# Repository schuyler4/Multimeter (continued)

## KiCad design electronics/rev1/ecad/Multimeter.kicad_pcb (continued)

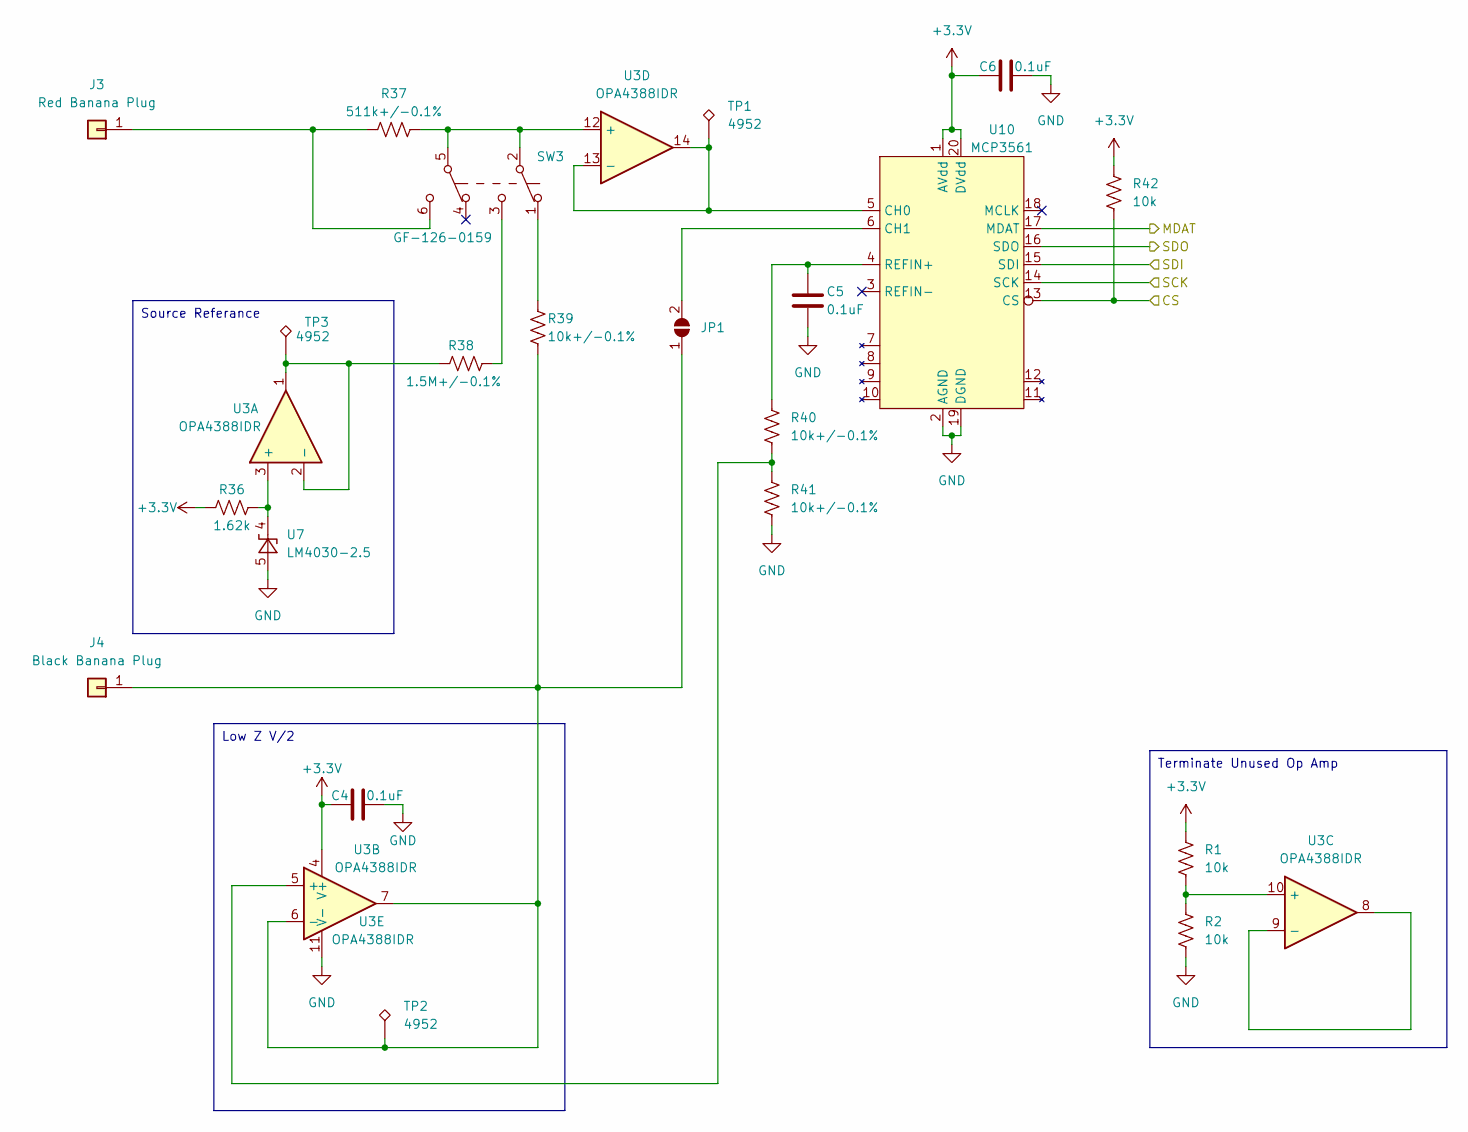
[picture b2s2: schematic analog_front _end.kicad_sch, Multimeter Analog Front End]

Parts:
C4, C5, C6: 0.1uF; C_0805_2012Metric; Part # CL21B104KBCNNNC; Digikey Part # 1276-1003-1-ND
J3: Red Banana Plug; KEYSTONE_575-4; Part # 575-8; Digikey Part # 36-575-8-ND
J4: Black Banana Plug; KEYSTONE_575-4; Part # 575-8; Digikey Part # 36-575-8-ND
JP1: SolderJumper-2_P1.3mm_Open_Pad1.0x1.5mm
R1, R2, R42: 10k; R_0805_2012Metric_Pad1.20x1.40mm_HandSolder; Part # RMCF0805FT10K0; Digikey Part # RMCF0805FT10K0CT-ND
R36: 1.62k; R_0805_2012Metric_Pad1.20x1.40mm_HandSolder; Part # RMCF0805FT1K62; Digikey Part # RMCF0805FT1K62CT-ND
R37: 511k+/-0.1%; R_0805_2012Metric_Pad1.20x1.40mm_HandSolder; Part # ERA-6AEB5113V; Digikey Part # P511KDACT-ND
R38: 1.5M+/-0.1%; R_0805_2012Metric_Pad1.20x1.40mm_HandSolder; Part # RG2012P-155-B-T5; Digikey Part # 408-2025-1-ND
R39, R40, R41: 10k+/-0.1%; R_0805_2012Metric_Pad1.20x1.40mm_HandSolder; Part # ERA-6AEB103V; Digikey Part # P10KDACT-ND
SW3: GF-126-0159; SW_GF-126-0159; Part # GF-126-0159; Digikey Part # SW342-ND
TP1, TP2, TP3: 4952; TestPoint_THTPad_1.5x1.5mm_Drill0.7mm; Part # 4952; Digikey Part # 36-4952-ND
U3: OPA4388IDR; SOIC-14_3.9x8.7mm_P1.27mm; Part # OPA4388IDR; Digikey Part # 296-53511-1-ND
U7: LM4030-2.5; SOT-23-5; Part # LM4030CMF-2.5/NOPB; Digikey Part # LM4030CMF-2.5/NOPBCT-ND
U10: MCP3561; SSOP-20_4.4x6.5mm_P0.65mm; Part # MCP3561RT-E/ST; Digikey Part # 150-MCP3561RT-E/STCT-ND

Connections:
+3.3V: C4.1, C6.1, R1.1, R36.1, R42.1, U3.4 (V+), U10.1 (AVdd), U10.20 (DVdd); also elsewhere on the board
/Analog Front End/CS: R42.2, U10.13 (CS); also elsewhere on the board
/Analog Front End/MDAT: U10.17 (MDAT); also elsewhere on the board
/Analog Front End/SCK: U10.14 (SCK); also elsewhere on the board
/Analog Front End/SDI: U10.15 (SDI); also elsewhere on the board
/Analog Front End/SDO: U10.16 (SDO); also elsewhere on the board
GND: C4.2, C5.2, C6.2, R2.2, R41.2, U3.11 (V-), U7.5 (A), U10.2 (AGND), U10.19 (DGND); also elsewhere on the board
unnamed: J3.1, R37.1, SW3.6 (C)
unnamed: J4.1, JP1.1 (A), R39.2, TP2.1, U3.6 (-), U3.7
unnamed: JP1.2 (B), U10.6 (CH1)
unnamed: R38.2, SW3.3 (C)
unnamed: R39.1, SW3.1 (A)
unnamed: R36.2, U3.3 (+), U7.4 (K)
unnamed: R38.1, TP3.1, U3.1, U3.2 (-)
unnamed: R40.2, R41.1, U3.5 (+)
unnamed: R1.2, R2.1, U3.10 (+)
unnamed: U3.8, U3.9 (-)
unnamed: R37.2, SW3.2 (B), SW3.5 (B), U3.12 (+)
unnamed: TP1.1, U3.13 (-), U3.14, U10.5 (CH0)
unnamed: C5.1, R40.1, U10.4 (REFIN+)

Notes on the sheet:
Low Z V/2
Terminate Unused Op Amp
Source Referance

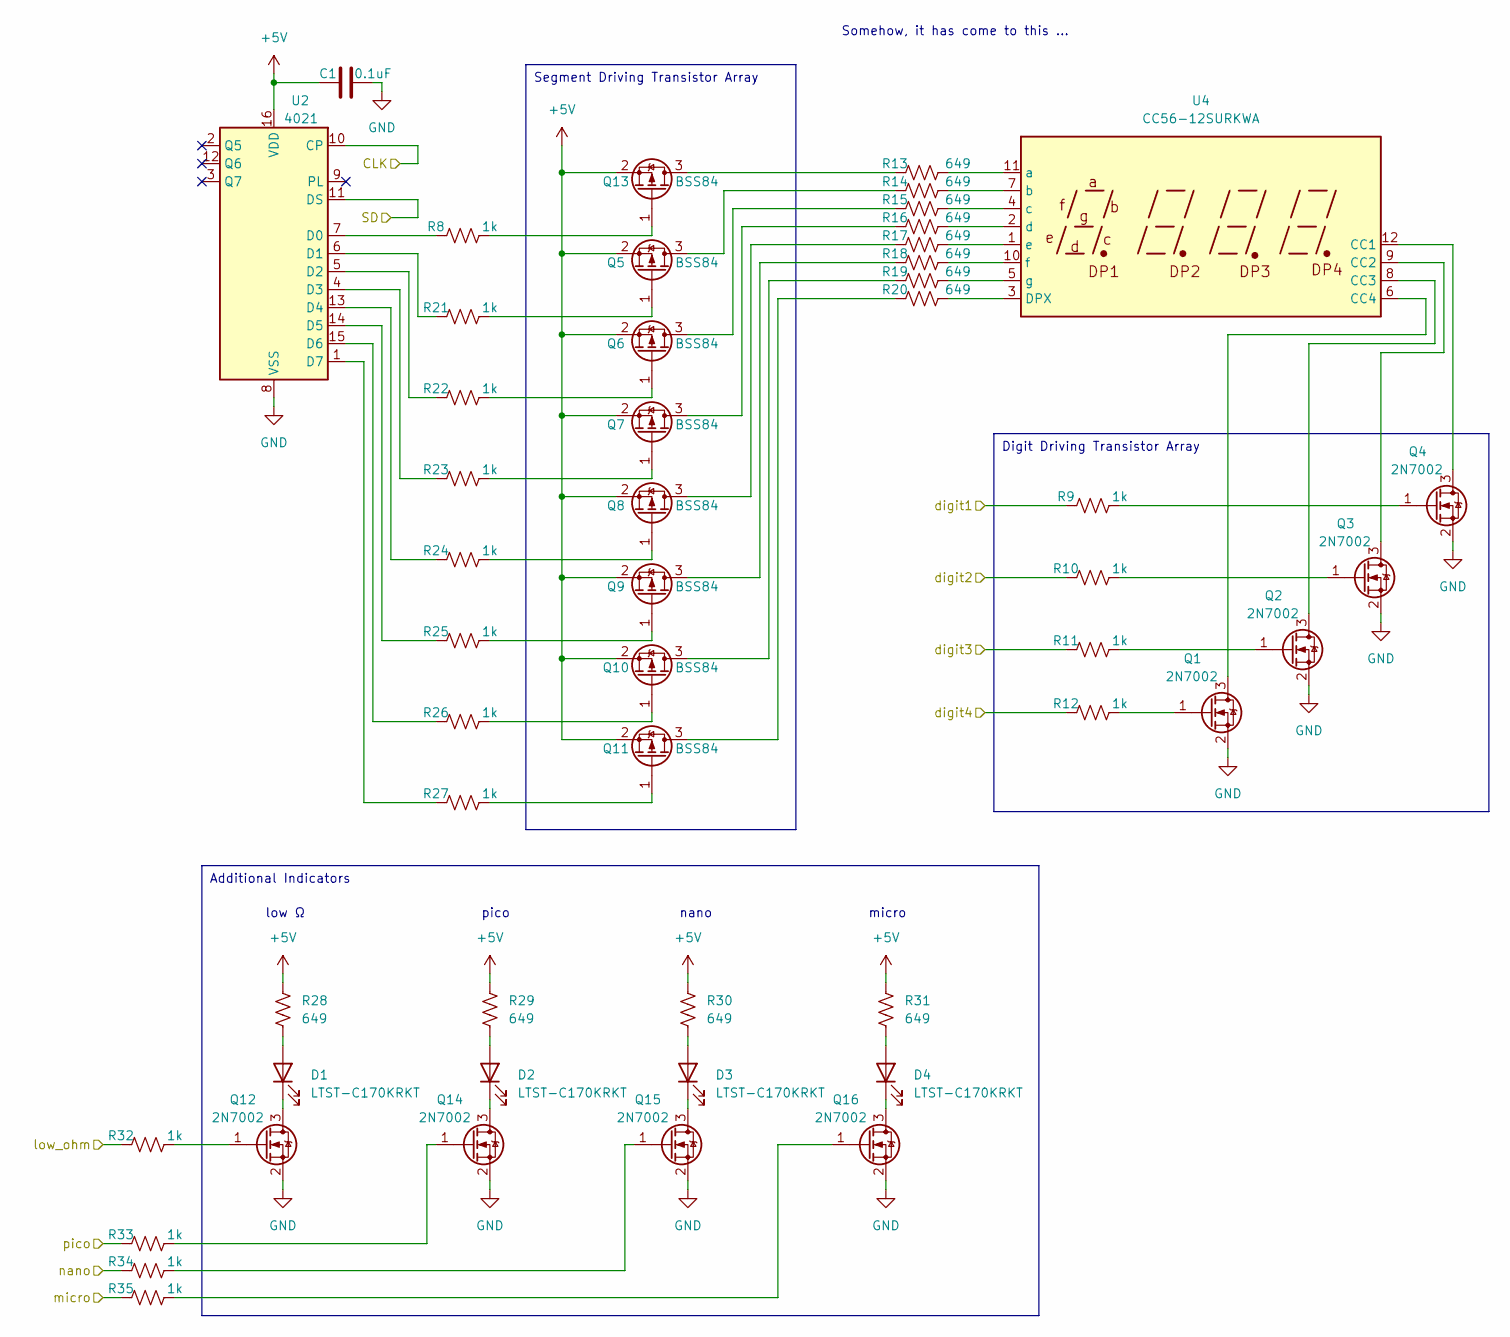
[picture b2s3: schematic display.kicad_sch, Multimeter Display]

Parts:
C1: 0.1uF; C_0805_2012Metric; Part # CL21B104KBCNNNC; Digikey Part # 1276-1003-1-ND
D1, D2, D3, D4: LTST-C170KRKT; LED_0805_2012Metric; Part # LTST-C170KRKT; Digikey Part # 160-1415-1-ND
Q1, Q2, Q3, Q4, Q12, Q14, Q15, Q16: 2N7002; SOT-23; Part # 2N7002; Digikey Part # 2N7002NCT-ND
Q5, Q6, Q7, Q8, Q9, Q10, Q11, Q13: BSS84; SOT-23; Part # BSS84; Digikey Part # 4786-BSS84CT-ND
R8, R9, R10, R11, R12, R21, R22, R23, R24, R25, R26, R27, R32, R33, R34, R35: 1k; R_0805_2012Metric_Pad1.20x1.40mm_HandSolder; Part # RMCF0805FT1K00; Digikey Part # RMCF0805FT1K00CT-ND
R13, R14, R15, R16, R17, R18, R19, R20, R28, R29, R30, R31: 649; R_0805_2012Metric_Pad1.20x1.40mm_HandSolder; Part # RMCF0805FT649R; Digikey Part # RMCF0805FT649RCT-ND
U2: 4021; SOIC-16_3.9x9.9mm_P1.27mm; Part # CD4021BM96; Digikey Part # 296-38905-1-ND
U4: CC56-12SURKWA; CA56-12SURKWA; Part # CC56-12SURKWA; Digikey Part # 754-CC56-12SURKWA-ND

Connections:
+5V: C1.1, Q5.2 (S), Q6.2 (S), Q7.2 (S), Q8.2 (S), Q9.2 (S), Q10.2 (S), Q11.2 (S), Q13.2 (S), R28.1, R29.1, R30.1, R31.1, U2.16 (VDD); also elsewhere on the board
/Display/CLK: U2.10 (CP); also elsewhere on the board
/Display/SD: U2.11 (DS); also elsewhere on the board
/Display/digit1: R9.1; also elsewhere on the board
/Display/digit2: R10.1; also elsewhere on the board
/Display/digit3: R11.1; also elsewhere on the board
/Display/digit4: R12.1; also elsewhere on the board
/Display/low_ohm: R32.1; also elsewhere on the board
/Display/micro: R35.1; also elsewhere on the board
/Display/nano: R34.1; also elsewhere on the board
/Display/pico: R33.1; also elsewhere on the board
GND: C1.2, Q1.2 (S), Q2.2 (S), Q3.2 (S), Q4.2 (S), Q12.2 (S), Q14.2 (S), Q15.2 (S), Q16.2 (S), U2.8 (VSS); also elsewhere on the board
unnamed: D1.2 (A), R28.2
unnamed: D1.1 (K), Q12.3 (D)
unnamed: D2.2 (A), R29.2
unnamed: D2.1 (K), Q14.3 (D)
unnamed: D3.2 (A), R30.2
unnamed: D3.1 (K), Q15.3 (D)
unnamed: D4.2 (A), R31.2
unnamed: D4.1 (K), Q16.3 (D)
unnamed: Q1.3 (D), U4.6 (CC4)
unnamed: Q1.1 (G), R12.2
unnamed: Q2.3 (D), U4.8 (CC3)
unnamed: Q2.1 (G), R11.2
unnamed: Q3.3 (D), U4.9 (CC2)
unnamed: Q3.1 (G), R10.2
unnamed: Q4.3 (D), U4.12 (CC1)
unnamed: Q4.1 (G), R9.2
unnamed: Q5.3 (D), R14.1
unnamed: Q5.1 (G), R21.2
unnamed: Q6.3 (D), R15.1
unnamed: Q6.1 (G), R22.2
unnamed: Q7.3 (D), R16.1
unnamed: Q7.1 (G), R23.2
unnamed: Q8.3 (D), R17.1
unnamed: Q8.1 (G), R24.2
unnamed: Q9.3 (D), R18.1
unnamed: Q9.1 (G), R25.2
unnamed: Q10.3 (D), R19.1
unnamed: Q10.1 (G), R26.2
unnamed: Q11.3 (D), R20.1
unnamed: Q11.1 (G), R27.2
unnamed: Q12.1 (G), R32.2
unnamed: Q13.3 (D), R13.1
unnamed: Q13.1 (G), R8.2
unnamed: Q14.1 (G), R33.2
unnamed: Q15.1 (G), R34.2
unnamed: Q16.1 (G), R35.2
unnamed: R8.1, U2.7 (D0)
unnamed: R21.1, U2.6 (D1)
unnamed: R22.1, U2.5 (D2)
unnamed: R23.1, U2.4 (D3)
unnamed: R24.1, U2.13 (D4)
unnamed: R25.1, U2.14 (D5)
unnamed: R26.1, U2.15 (D6)
unnamed: R27.1, U2.1 (D7)
unnamed: R20.2, U4.3 (DPX)
unnamed: R13.2, U4.11 (a)
unnamed: R14.2, U4.7 (b)
unnamed: R15.2, U4.4 (c)
unnamed: R16.2, U4.2 (d)
unnamed: R17.2, U4.1 (e)
unnamed: R18.2, U4.10 (f)
unnamed: R19.2, U4.5 (g)

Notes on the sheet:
Segment Driving Transistor Array
Digit Driving Transistor Array
Additional Indicators
nano
pico
Somehow, it has come to this ...
low Ω
micro

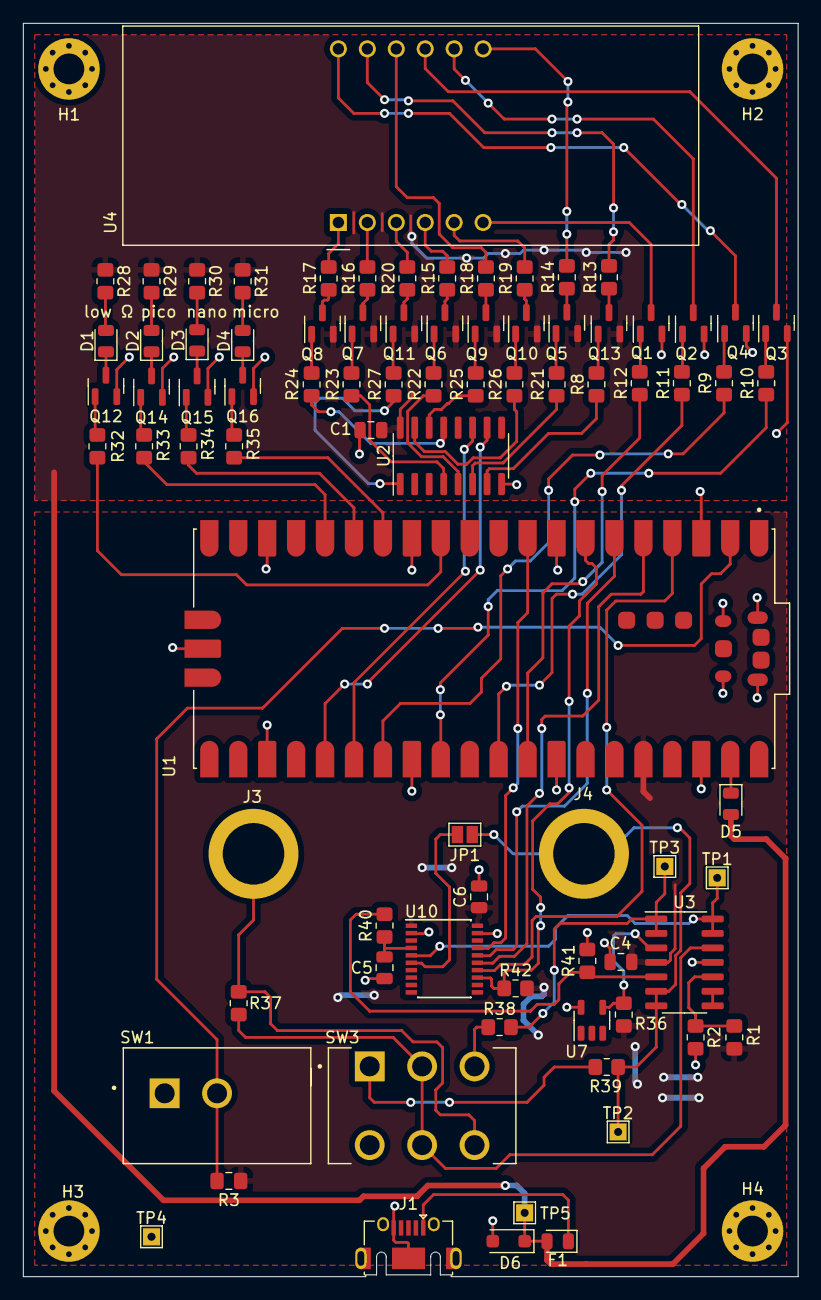
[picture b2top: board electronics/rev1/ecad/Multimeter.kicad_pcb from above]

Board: 2 copper layers, 68.0 x 110.0 mm, 86 parts (0 on the bottom side), 86 nets.

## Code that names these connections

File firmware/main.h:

//
// FILENAME: main.h
//
// DESCRIPTION: This is the header file for main.c. Pin Definitions
// and high level measurement function prototypes are included. 
//
// Written by Marek Newton
// 

#ifndef MAIN_H
#define MAIN_H

#include "calcs.h"

#define REVISION 1

#define CS_PIN 5
#define SCK_PIN 2
#define MOSI_PIN 3 // MASTER OUT SLAVE IN 
#define MISO_PIN 4 // MASTER IN SLAVE OUT
#define CHIP_SELECT_PIN 5

#define DATA_INTERUPT_PIN 6

#if REVISION == 1

#define DIGIT1_PIN 21
#define DIGIT2_PIN 22
#define DIGIT3_PIN 26
#define DIGIT4_PIN 27

#define SEGMENT_A_PIN 13
#define SEGMENT_B_PIN 14
#define SEGMENT_C_PIN 17
#define SEGMENT_D_PIN 19
#define SEGMENT_E_PIN 20
#define SEGMENT_F_PIN 16
#define SEGMENT_G_PIN 15
#define SEGMENT_DP_PIN 18

#else

#define DIGIT1_PIN 13
#define DIGIT2_PIN 14
#define DIGIT3_PIN 15
#define DIGIT4_PIN 16

#define SEGMENT_A_PIN 28 

#define SEGMENT_B_PIN 27
#define SEGMENT_C_PIN 26
#define SEGMENT_D_PIN 22
#define SEGMENT_E_PIN 21
#define SEGMENT_F_PIN 20
#define SEGMENT_G_PIN 19
#define SEGMENT_DP_PIN 18

#define MODE_PIN 7
#define COMPONENT_MODE_PIN 1
#define RANGE_PIN 8

#define VOLTAGE_POSITIVE_CALIBRATION_OFFSET 0.00
#define VOLTAGE_NEGATIVE_CALIBRATION_OFFSET 0.00

#endif

#define CAP_TRIGGER_PIN 12
#define NANO_PIN 11
#define MICRO_PIN 10
#define LOW_OHM_AND_NEGATIVE_PIN 9

#define SPI_SCK_FREQ 2000000

#define AVERAGE_READING_COUNT 200

#define CAPACITANCE_VOLTAGE_THRESHOLD_HIGH 1
#define CAPACITANCE_VOLTAGE_THRESHOLD_LOW 0.01

typedef enum
{
    Voltage,
    Resistance, 
    Capacitance
} Mode;

typedef struct 
{
    double magnitude;
    uint8_t sign;
} Signed_Voltage;

void setup_SPI(void);
void setup_IO(void);

void sample_resistance(void);
void sample_voltage(void);
void sample_capacitance(void);

void display_reading(void);

#endif

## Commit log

2024-01-04 start of schematic
2024-01-08 stuff
2024-01-12 fully simulated cap measure
2024-01-13 cap interpolation test
2024-01-21 layout finished
2024-01-21 gerbers
2024-02-12 ADC Driver Work
2024-02-14 removed ignored files
2024-02-14 removed line on readme
2024-02-22 ADC work
2024-02-23 ADC stuff
2024-02-25 display
2024-02-26 display hardware is wrong
2024-03-01 layout
2024-03-01 started export script
2024-03-03 firmware work
2024-03-04 good voltage and resistance
2024-03-04 export
2024-03-05 resistance reading
2024-03-05 some stuff
2024-03-06 nothing is working
2024-03-06 working again
2024-03-06 docs and stuff
2024-03-06 typo
2024-03-07 capacitance start
2024-03-07 python cap calc
2024-03-08 rough capacitance measurement
2024-03-10 preliminary test
2024-03-12 display doing stuff
2024-03-13 dislay reading voltage
2024-03-14 ordered some stuff
2024-03-20 proper sign on average voltage
2024-03-20 readme update
2024-03-21 voltage reading and calibration
2024-03-22 start of rev2 code
2024-03-23 resistance stuff
2024-03-26 display stuff
2024-04-02 remove file
2024-04-05 adjustment
2024-04-07 capacitance reading
2024-04-09 much more accurate voltage measurement
2024-04-10 resistance cal
2024-04-10 capacitance stuff
2024-04-14 rev2 cal
2024-04-17 back to rev1
2024-04-18 rev1 cal
2025-05-29 rev3 start
2025-06-02 cal2 and pictures
2025-06-02 correct picture and update specs
2025-08-14 rev3 schematic work
2025-08-16 layout work rev3
2025-08-17 layout complete
2025-08-19 rev3 work
2025-09-11 started firmware2
2025-09-15 firmware2 work
2025-09-15 remove capacitance stuff
2025-09-21 auto range work
2025-09-24 work
2025-09-24 started convolution
2025-09-24 added running average
2025-09-27 diode mode
2025-10-13 removed zeroing
2025-12-22 work and calibration
2025-12-23 refactor
2025-12-23 fdsaf
2026-05-08 started rev4
